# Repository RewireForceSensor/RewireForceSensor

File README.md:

# RewireForceSensor
A project for the Rewire Robotics Laboratory at UT Austin. Contains Android Studio code for our custom app as well as Arduino code for both iterations of the footplate and the PCB design for the Load Cell version of the footplate.

Built with Dr. James Sulzer by undergraduate students Timothy Pollard-Grayson, Corbin Capo, and Ishan Deshpande

Special thanks to Trey Crisco

# Project Description
Footplate designed for a patient in a medical stander, in order to monitor foot and pressure information. Uses bluetooth to communicate to an app where a physical
therapist can actively and passively keep track of the patient's progress.

# Relevant Links
[App Releases](https://github.com/RewireForceSensor/RewireForceSensor/releases)

[Atlantic Article](https://www.theatlantic.com/magazine/archive/2021/11/engineers-daughter-tbi-rehab/620172/)

[UT Engineering Article](https://cockrell.utexas.edu/news/archive/9435-a-personal-experience-galvanizes-rehab-tech-researchers)

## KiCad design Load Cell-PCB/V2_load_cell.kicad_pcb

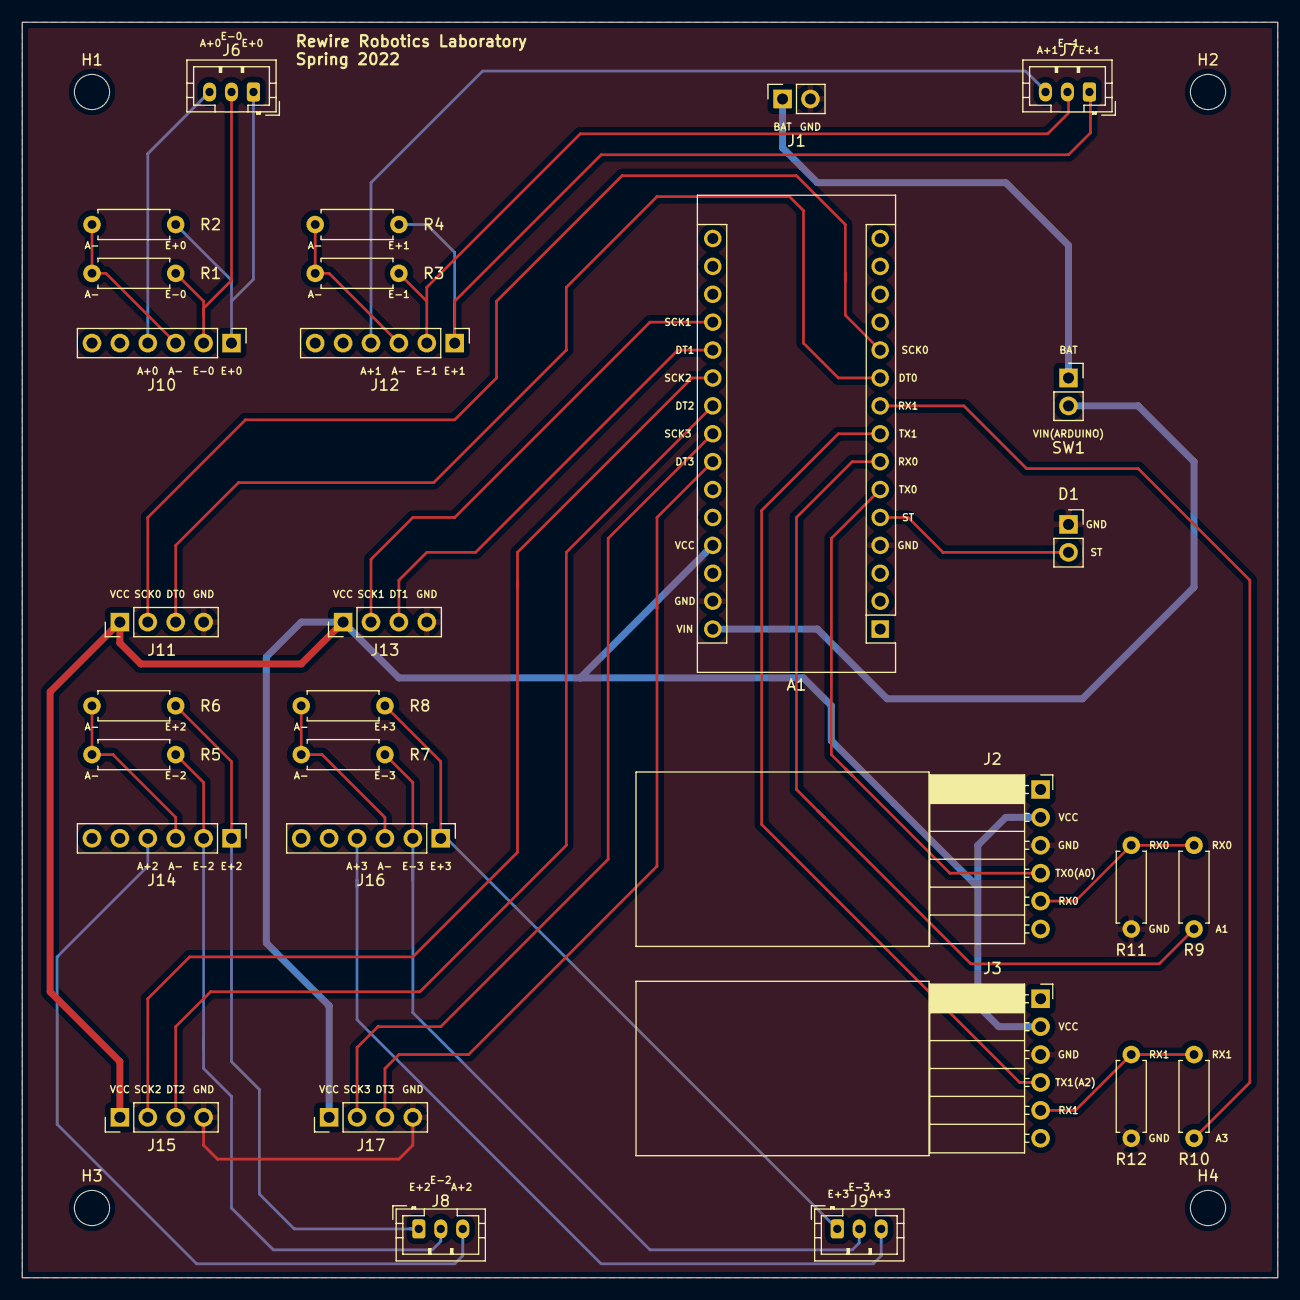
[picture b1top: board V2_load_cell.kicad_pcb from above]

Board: 2 copper layers, 114.3 x 114.3 mm, 34 parts (0 on the bottom side), 35 nets.

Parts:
A1: Arduino_Nano_Every; Arduino_Nano
D1: LED; PinSocket_1x02_P2.54mm_Vertical
H1, H2, H3, H4: MountingHole; MountingHole_3.2mm_M3
J1: Conn_01x02; PinSocket_1x02_P2.54mm_Vertical
J2, J3: Conn_01x06; PinSocket_1x06_P2.54mm_Horizontal
J6, J7, J8, J9: Conn_01x03; JST_PH_B3B-PH-K_1x03_P2.00mm_Vertical
J10, J12, J14, J16: Conn_01x06; PinHeader_1x06_P2.54mm_Vertical
J11, J13, J15, J17: Conn_01x04; PinHeader_1x04_P2.54mm_Vertical
R1, R2, R3, R4, R5, R6, R7, R8, R9, R10: 1k; R_Axial_DIN0207_L6.3mm_D2.5mm_P7.62mm_Horizontal
R11, R12: 2k; R_Axial_DIN0207_L6.3mm_D2.5mm_P7.62mm_Horizontal
SW1: SW_DIP_x01; PinSocket_1x02_P2.54mm_Vertical

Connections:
/A+0: J6.3, J10.4
/A+1: J7.3, J12.4
/A+2: J8.3, J14.4
/A+3: J9.3, J16.4
/DT0: A1.10, J11.3
/DT1: A1.20, J13.3
/DT2: A1.22, J15.3
/DT3: A1.24, J17.3
/E+0: J6.1, J10.1, R2.2
/E+1: J7.1, J12.1, R4.2
/E+2: J8.1, J14.1, R6.2
/E+3: J9.1, J16.1, R8.2
/E-0: J6.2, J10.2, R1.2
/E-1: J7.2, J12.2, R3.2
/E-2: J8.2, J14.2, R5.2
/E-3: J9.2, J16.2, R7.2
/RX0: A1.7, R9.2
/RX0R: J2.5, R9.1, R11.1
/RX1: A1.9, R10.2
/RX1R: J3.5, R10.1, R12.2
/SCK0: A1.11, J11.2
/SCK1: A1.19, J13.2
/SCK2: A1.21, J15.2
/SCK3: A1.23, J17.2
/ST: A1.5, D1.2
/Sheet61D3CBFB/A-: J10.3, R1.1, R2.1
/TX0: A1.6, J2.4
/TX1: A1.8, J3.4
/VIN: A1.30, SW1.2
/sheet61D4E250/A-: J12.3, R3.1, R4.1
/sheet61D4EE5D/A-: J14.3, R5.1, R6.1
/sheet61D4FC90/A-: J16.3, R7.1, R8.1
BAT: J1.1, SW1.1
GND: A1.4, A1.29, D1.1, J1.2, J2.3, J3.3, J11.4, J13.4, J15.4, J17.4, R11.2, R12.1
VCC: A1.27, J2.2, J3.2, J11.1, J13.1, J15.1, J17.1

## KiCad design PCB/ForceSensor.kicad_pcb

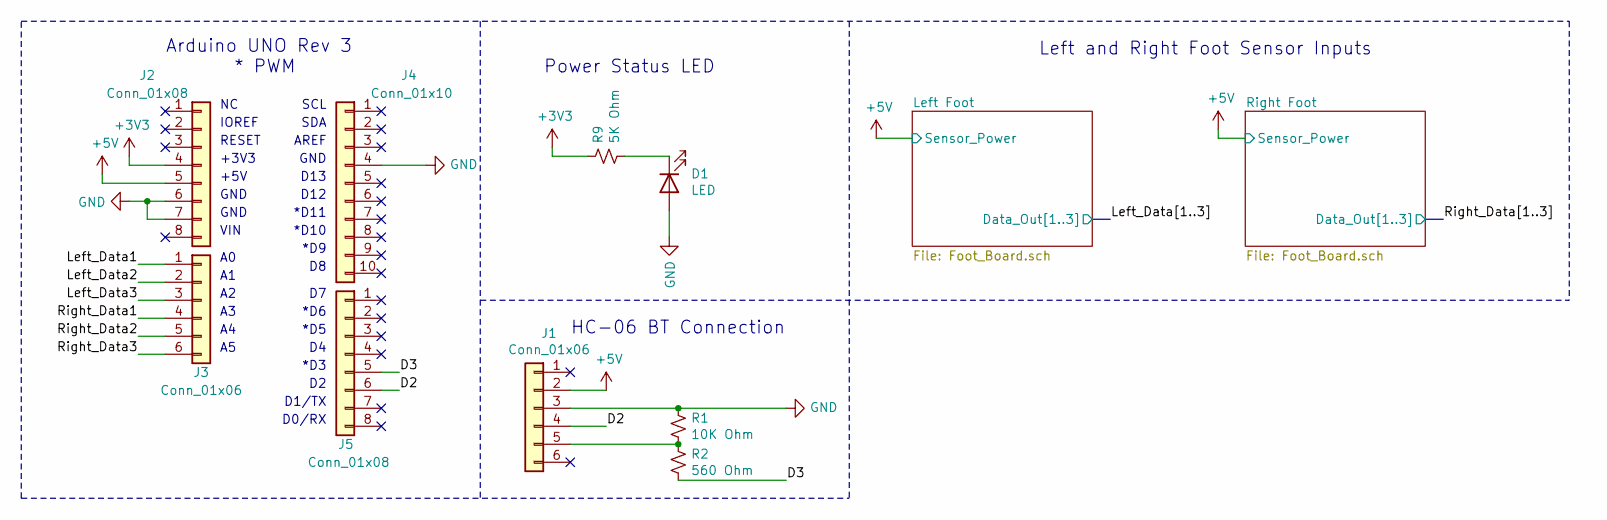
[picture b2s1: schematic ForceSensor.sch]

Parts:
D1: LED; D_T-1_P2.54mm_Vertical_AnodeUp
J1, J3: Conn_01x06; PinHeader_1x06_P2.54mm_Vertical
J2, J5: Conn_01x08; PinHeader_1x08_P2.54mm_Vertical
J4: Conn_01x10; PinHeader_1x10_P2.54mm_Vertical
R1: 10K Ohm; R_Axial_DIN0207_L6.3mm_D2.5mm_P7.62mm_Horizontal
R2: 560 Ohm; R_Axial_DIN0207_L6.3mm_D2.5mm_P7.62mm_Horizontal
R9: 5K Ohm; R_Axial_DIN0207_L6.3mm_D2.5mm_P7.62mm_Horizontal

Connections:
+3V3: J2.4, R9.1
+5V: J1.2, J2.5; also elsewhere on the board
/D2: J1.4, J5.6
/D3: J5.5, R2.2
/Left_Data1: J3.1; also elsewhere on the board
/Left_Data2: J3.2; also elsewhere on the board
/Left_Data3: J3.3; also elsewhere on the board
/Right_Data1: J3.4; also elsewhere on the board
/Right_Data2: J3.5; also elsewhere on the board
/Right_Data3: J3.6; also elsewhere on the board
GND: D1.2 (A), J1.3, J2.6, J2.7, J4.4, R1.1; also elsewhere on the board
unnamed: D1.1 (K), R9.2
unnamed: J1.5, R1.2, R2.1

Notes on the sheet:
Arduino UNO Rev 3 * PWM
IOREF
RESET
+3V3
+5V
GND
VIN
SCL
SDA
AREF
D13
D12
*D11
*D10
*D9
*D6
*D5
*D3
D1/TX
D0/RX
HC-06 BT Connection
Left and Right Foot Sensor Inputs
Power Status LED

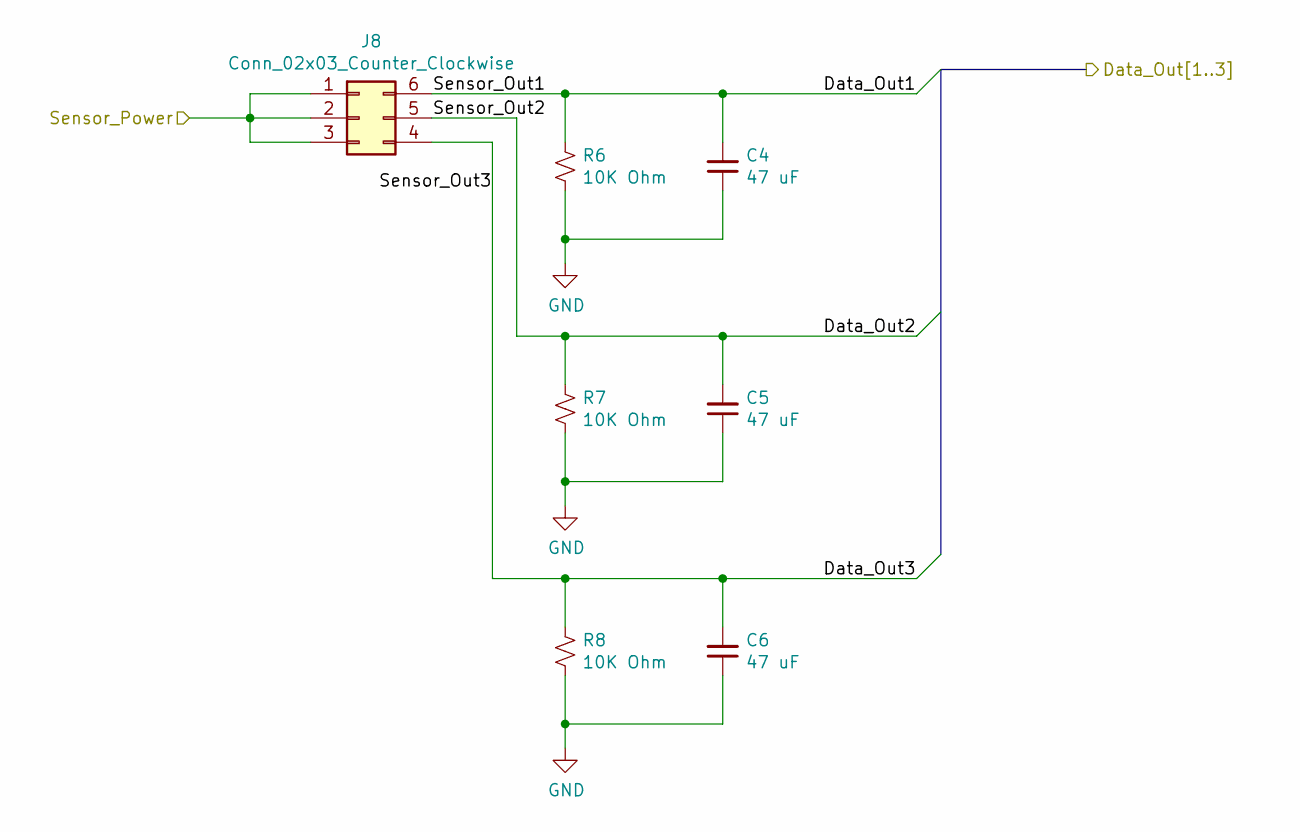
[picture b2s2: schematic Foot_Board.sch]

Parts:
C1, C2, C3: 47 uF; CP_Radial_D5.0mm_P2.50mm
J7: Conn_02x03_Counter_Clockwise; Molex_Micro-Fit_3.0_43045-0600_2x03_P3.00mm_Horizontal
R3, R4, R5: 10K Ohm; R_Axial_DIN0207_L6.3mm_D2.5mm_P7.62mm_Horizontal

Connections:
+5V: J7.1, J7.2, J7.3; also elsewhere on the board
/Left_Data1: C1.2, J7.6, R3.1; also elsewhere on the board
/Left_Data2: C2.2, J7.5, R4.1; also elsewhere on the board
/Left_Data3: C3.2, J7.4, R5.1; also elsewhere on the board
GND: C1.1, C2.1, C3.1, R3.2, R4.2, R5.2; also elsewhere on the board

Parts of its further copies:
C4, C5, C6: 47 uF; CP_Radial_D5.0mm_P2.50mm
J8: Conn_02x03_Counter_Clockwise; Molex_Micro-Fit_3.0_43045-0600_2x03_P3.00mm_Horizontal
R6, R7, R8: 10K Ohm; R_Axial_DIN0207_L6.3mm_D2.5mm_P7.62mm_Horizontal

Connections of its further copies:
+5V: J8.1, J8.2, J8.3; also elsewhere on the board
/Right_Data1: C4.2, J8.6, R6.1; also elsewhere on the board
/Right_Data2: C5.2, J8.5, R7.1; also elsewhere on the board
/Right_Data3: C6.2, J8.4, R8.1; also elsewhere on the board
GND: C4.1, C5.1, C6.1, R6.2, R7.2, R8.2; also elsewhere on the board

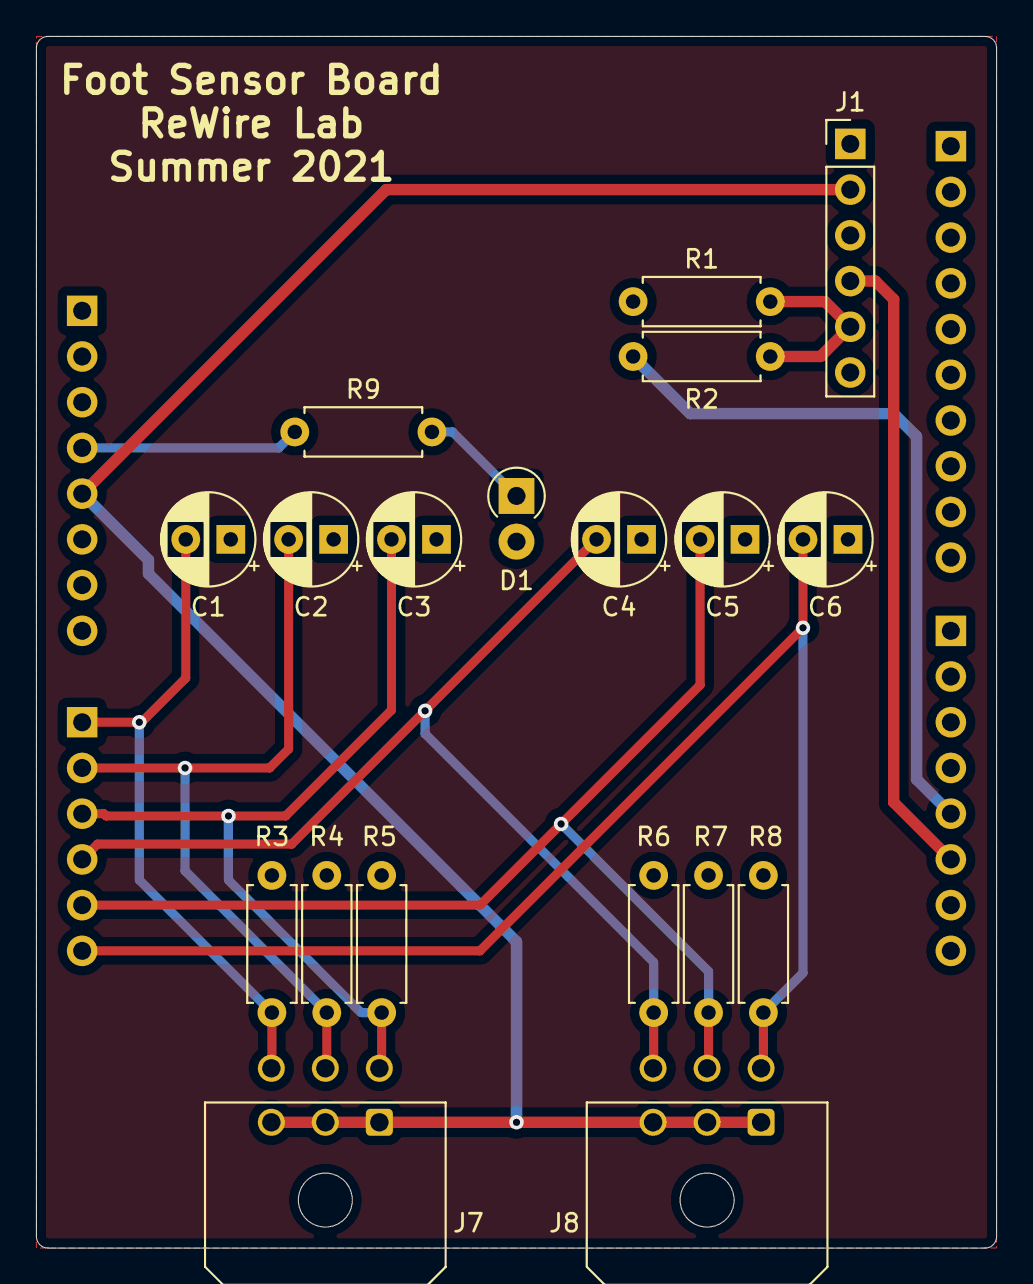
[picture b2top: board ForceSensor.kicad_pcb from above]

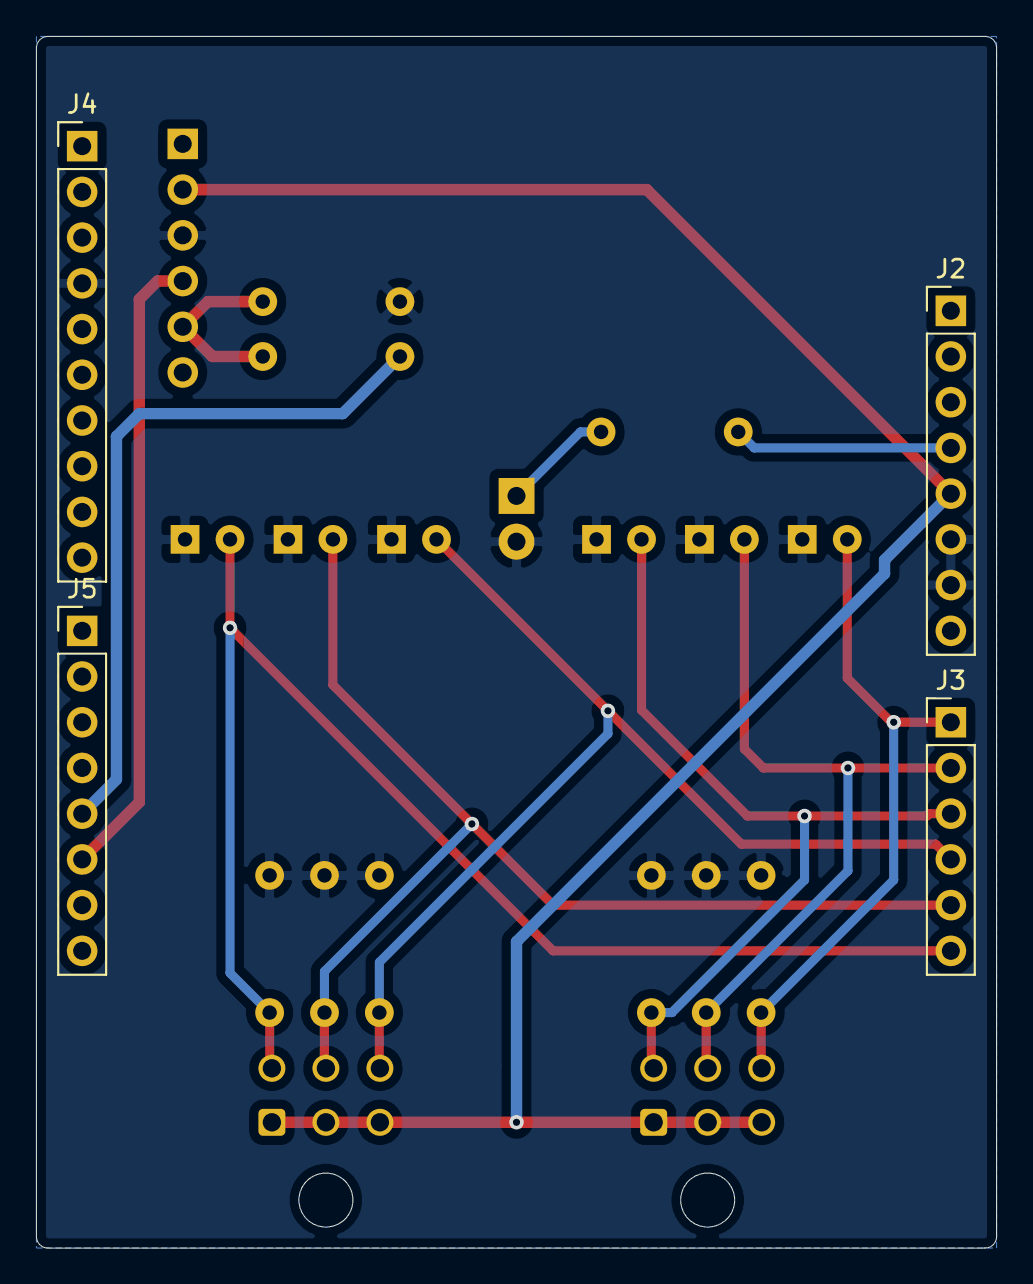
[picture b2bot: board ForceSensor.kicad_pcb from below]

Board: 2 copper layers, 53.3 x 67.3 mm, 23 parts (4 on the bottom side), 13 nets.

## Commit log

2021-07-26 init
2021-07-26 wrote some code
2021-07-30 Code reorganized and new android app, arduino file added
2021-08-03 Added heatmap library
2021-08-03 Now I have SDK
2021-08-03 added some feet into xml
2021-08-04 added code for sending and reading multiple flexiforce values
2021-08-04 fixed xml upload
2021-08-04 added textboxes to xml
2021-08-04 Added code to update text boxes with correct FSR values
2021-08-06 got one foot working
2021-08-06 removed obsolete android app, got app working with 6 sensors and calibrated force sensors to give more accurate readings
2021-08-07 added launcher icon
2021-08-10 Added data logging to CSV, untested
2021-08-13 adding branch for Corbin
2021-08-16 adding progbar for r/l comparison
2021-08-16 working on fixing file creation
2021-08-16 removed v2-android-app
2021-08-16 Deleted old folder
2021-08-16 adding progbar
2021-08-16 Adding kiCad pcb files
2021-08-16 Deleted old files
2021-08-16 added port/starboard coloring to the feet as well as fixed the progress bar issues
2021-08-16 New schematic
2021-08-16 still working on resolving filewriter issues
2021-08-16 deleting vestigial files
2021-08-17 File creation and logging works, yet to be tested with logging data points and currently exports into Downloads/RewireForceSensor/
2021-08-17 added moving 3 point average and rounding
2021-08-17 Added schematics for rfs pcb
2021-08-18 Finished schematic
2021-08-18 Small changes to schematic
2021-08-19 adding notification framework
2021-08-19 minor bugfixes and finalized 3 point average & progress bar
2021-08-19 File creation and writing has been switched to the storage access framework, everything works. Connect button disables when connected and log button does not work when disconnected.
2021-08-20 Rough layout of pcb
2021-08-20 added cycle count to csv data logging
2021-08-25 fixed cycle count newline issue and tested logging
2021-08-25 Edits for tolerances
2021-08-28 Added power LED
2021-09-10 Gerber Baby sends his best
2021-09-14 Migrated foot data view code to new fragment, created abstract generic class for all data view fragments (such as graphs that will be added in the future), created OverviewFragment
2021-09-14 View looks OK in app, bugs fixed, but background feet need to be converted into separate images so as to better place the feet inside the overall view
2021-09-15 Reconstrained elements in overview_fragment.xml and made labels visible, split left and right sole into two elements for better alignment
2021-09-15 Revert "Merge pull request #7 from RewireForceSensor/rfs-35"
    This reverts commit 3d6e5db7314915ede12208de9352f1bd5f08c2c8, reversing
    changes made to 296bc6b0760cfac73721a09920a04b30bd9cc926.
    reverting so i can merge properly
2021-09-15 commit in order to remerge
2021-09-15 Revert "Rfs 35"
2021-09-15 fixed small file error thingy
2021-09-23 added heat map library, small bug involving position of heat map data points needs to be fixed
2021-09-23 wrote better three-point moving average code and better sensor data array format (now stored in integers instead of strings)
2021-09-24 Looked through realtime chart example and began Pronation/Supination chart creation
2021-09-24 changed int[] to double[] for storage of sensor data (comes from arduino as a double)
2021-09-24 fixed various issues regarding passing data to fragments that were causing app to crash
2021-09-24 configured some chart settings to make it look better. chart is working but still needs more configuration and a second data set.
2021-09-27 Pronation/Supination graph is now configured with proper styling to display supination vs pronation of both feet.
2021-09-30 - Restructured fragments that graph things under umbrella of GraphViewFragment - Repositioned XML to look better - Added Anterior/Posterior Fragment - Added Title for each view
2021-09-30 Overall balance view created and added, some graphs repositioned in order to see legend and all data clearly
2021-09-30 changed fragment linked to LeftRightFragment class
2021-09-30 added buttons, infinite scroll does not look good (yet)
2021-10-03 scrolling now operates on buttons only, title changes when you scroll, and infinite scrolling is enabled.
2021-10-04 fixed x-axis graphing issue
2021-10-04 added disconnect button, with clearing of fragments and logging support
2021-10-04 changed size of disconnect button
2021-10-08 dropdown title still not working completely
2021-10-17 scales forever instead of scrolling
2021-11-05 latest notification code that doesn't work
2021-11-05 small bugfixes for 11-7 test session with livvie
2022-01-17 zero weight notification works ok, full screen notification must be debugged.
2022-01-17 Successfully created a new fragment and boolean for the load cell in which we can draw custom things. Sizing of view inside LoadCellFragment needs to be fixed.
2022-01-30 Fixing some fragment view things
2022-01-30 Fixed some fragment view things
2022-02-16 view stuff
2022-02-16 initial commit of pcb v1
2022-02-17 2-17-22
2022-02-21 pcb v2 update
2022-02-23 JST connectors, increased track width of VCC, moved bluetooth modules, other small fixes
2022-02-25 I have no idea what is going on
2022-02-28 Changes: - Moved mounting holes - Changed size of HC-05 footprint marker - Moved one trace in the bottom left corner - Redid STEP, Gerber, Drill files
2022-02-28 should have fixed some trace clearance issues
2022-03-01 updated code
2022-03-01 changed some labels for bluetooth modules and redid tx/rx traces, flipped JST to be on top again
2022-03-01 added new zip
2022-03-01 Revert "updated code"
    This reverts commit 557b8297daa585503114d82b32e451c799d018f5.
2022-03-01 changed some labels, redid traces, flipped JST, new zip
2022-03-25 gerbers
2022-03-31 8 random numbers from board 1
2022-04-01 display of load cell data working
2022-04-04 fixed logging button not disabling after disconnect
2022-04-04 updated board code
2022-04-04 Rfs 52 (#20)
    * Successfully created a new fragment and boolean for the load cell in which we can draw custom things. Sizing of view inside LoadCellFragment needs to be fixed.
    * Fixing some fragment view things
    * Fixed some fragment view things
    * view stuff
    * initial commit of pcb v1
    * 2-17-22
2022-04-06 Final version of the code for test on 4/5/22
2022-04-11 Added catch for NumberFormatException, when arduino sometimes skips numbers/doesn't transfer correctly. Also fixed connectStatus to display correct info.
2022-04-11 Added log message on number format error; fixed disconnect text overflow
2022-04-11 Number Format Exception Handled (#22)
    * Added catch for NumberFormatException, when arduino sometimes skips numbers/doesn't transfer correctly. Also fixed connectStatus to display correct info.
    * Added log message on number format error; fixed disconnect text overflow
2022-04-11 merged in arduino-loadcell changes
2022-04-11 Lots of progress on calibration routine
2022-04-12 calibration routine finished
2022-04-13 fixed some stuff
2022-04-14 fixed some more stuff
2022-04-14 Rfs 59 (#23)
    * merged in arduino-loadcell changes
    * Lots of progress on calibration routine
    * calibration routine finished
    * fixed some stuff
    * fixed some more stuff
2022-04-14 added progress bar
2022-04-15 made significant progress on center of pressure. conversion to absolute coordinates is still crappy because of the clamping, but it works OK ish
2022-04-17 worked on fixing COP
2022-04-18 added floor so that data cannot go below 0.
2022-04-18 Add center of pressure (#24)
    * added progress bar
    * made significant progress on center of pressure. conversion to absolute coordinates is still crappy because of the clamping, but it works OK ish
    * worked on fixing COP
    * added floor so that data cannot go below 0.
2022-04-18 fixed clamping of cop dot to not go past edges of load cell on screen, and fixed what to do when app receives bad data
2022-04-18 fixed clamping of cop dot to not go past edges of load cell on screen, and fixed what to do when app receives bad data (#25)
